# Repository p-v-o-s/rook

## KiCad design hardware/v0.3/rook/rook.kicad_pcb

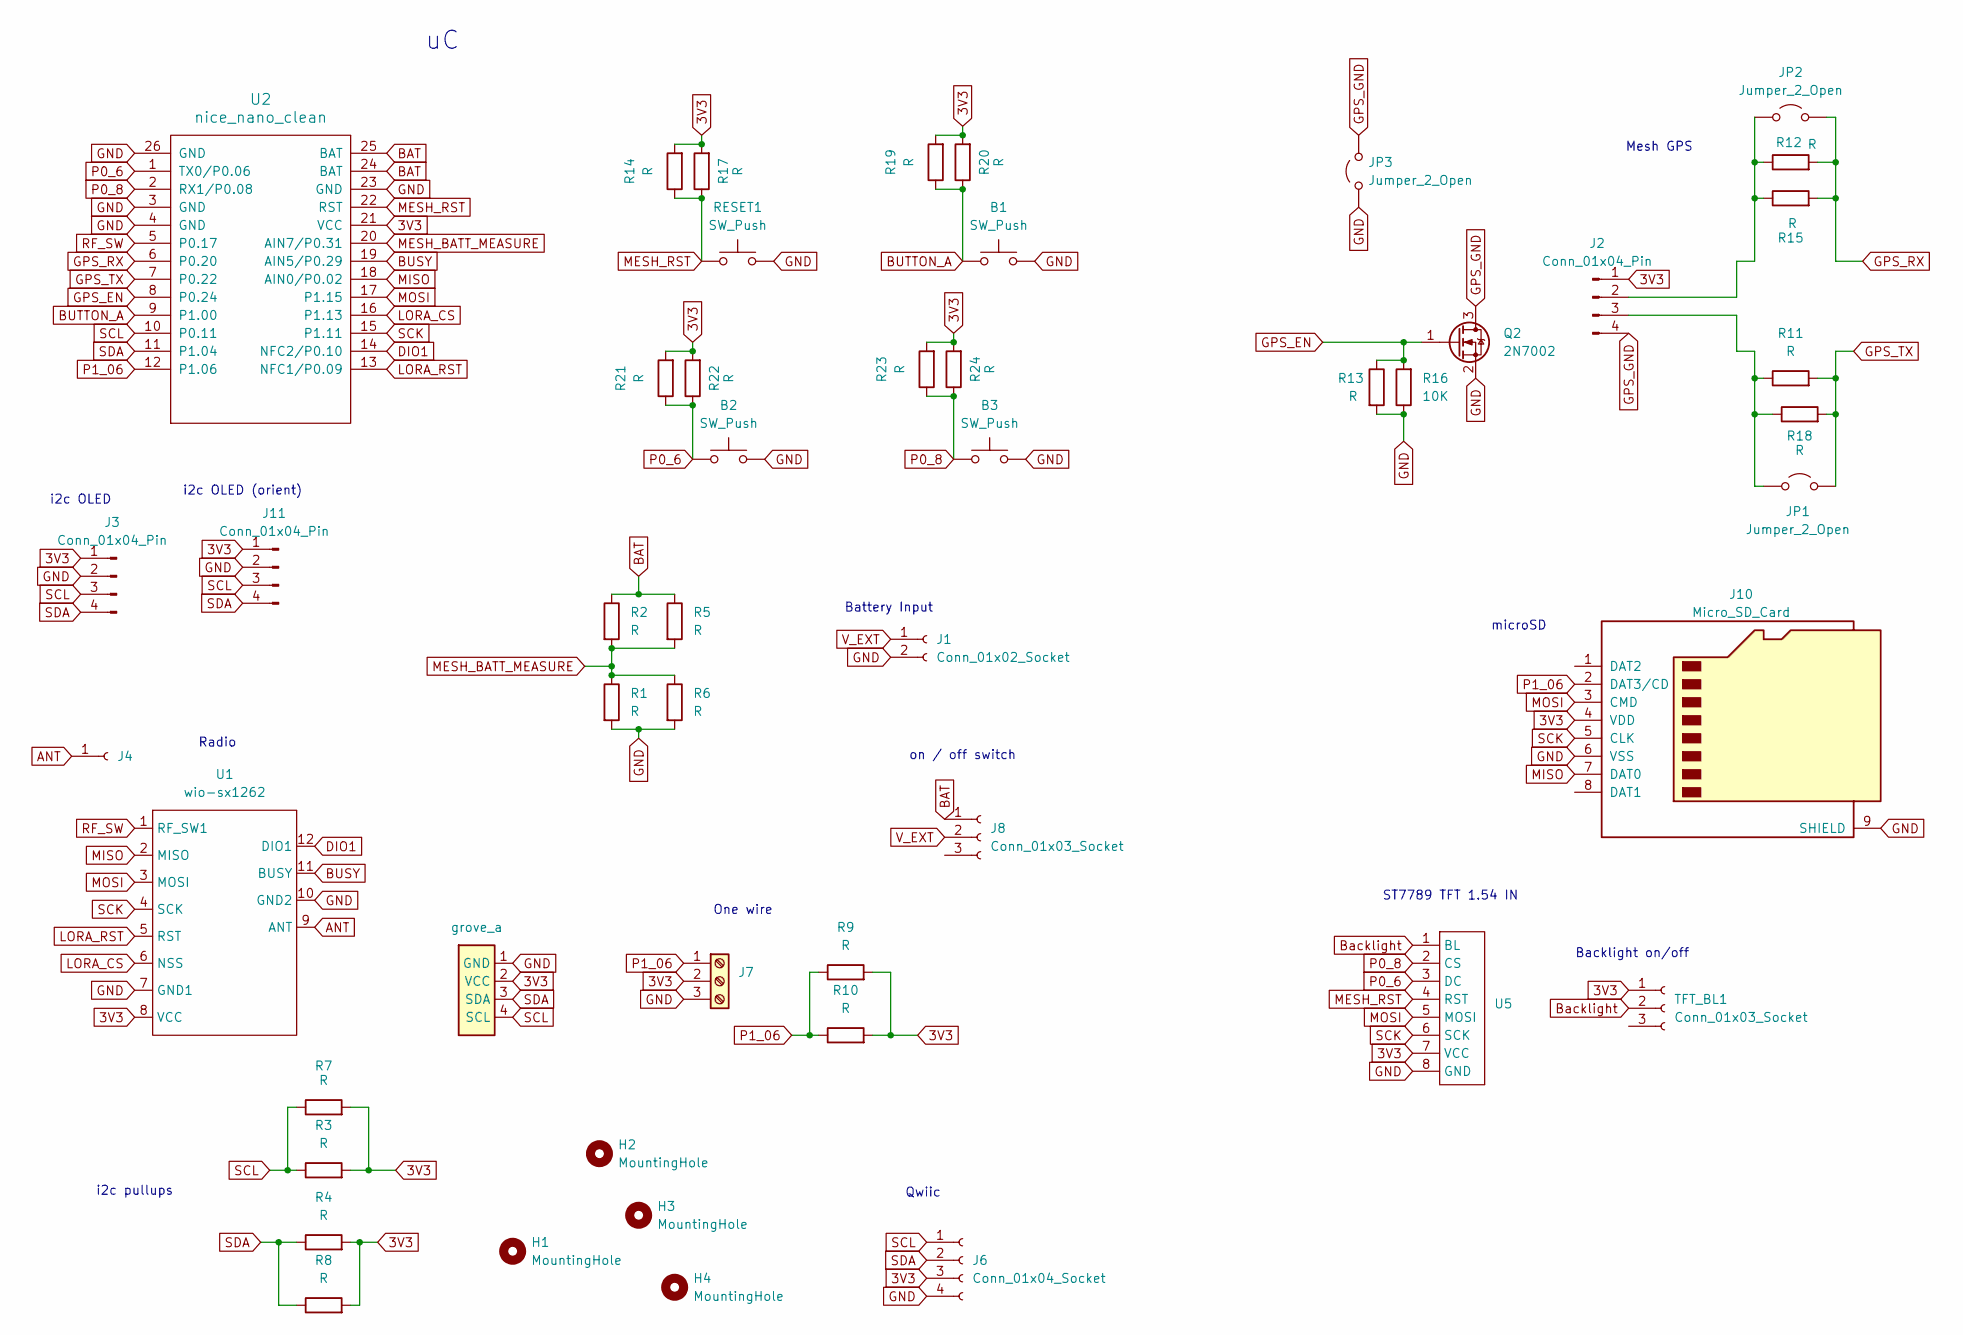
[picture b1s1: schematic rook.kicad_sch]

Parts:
B1, B2, B3: SW_Push; SW_Tactile_SPST_Angled_PTS645Vx31-2LFS
H1, H2, H3, H4: MountingHole; MountingHole_3.2mm_M3
J1: Conn_01x02_Socket; JST_PH_B2B-PH-K_1x02_P2.00mm_Vertical
J2: Conn_01x04_Pin; gps_ublox_blue
J3, J11: Conn_01x04_Pin; ssd1306_a
J4: Conn_01x01_Socket; PinSocket_1x01_P2.54mm_Vertical
J6: Conn_01x04_Socket; JST_SH4_SKINNY
J7: Screw_Terminal_01x03; TerminalBlock_Phoenix_MKDS-1,5-3-5.08_1x03_P5.08mm_Horizont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
J8: Conn_01x03_Socket; SSW_1825232-1
J10: Micro_SD_Card; DM3D-SF_outline
JP1, JP2, JP3: Jumper_2_Open; SolderJumper-2_P1.3mm_Open_Pad1.0x1.5mm
Q2: 2N7002; SOT-23
R1, R2, R3, R4, R10, R11, R12, R13, R14, R19, R21, R23: R; R_Axial_DIN0207_L6.3mm_D2.5mm_P10.16mm_Horizontal
R5, R6, R7, R8, R9, R15, R17, R18, R20, R22, R24: R; R_0805_2012Metric_Pad1.20x1.40mm_HandSolder
R16: 10K; R_0805_2012Metric_Pad1.20x1.40mm_HandSolder
RESET1: SW_Push; SW_Tactile_SPST_Angled_PTS645Vx31-2LFS
TFT_BL1: Conn_01x03_Socket; SSW_1825232-1
U1: wio-sx1262; wio-sx1262-extended
U2: nice_nano_clean; nice_nano_cleanest
U4: grove_a
U5: st7789_154in_240x240

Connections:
3V3: J2.1, J3.1, J6.3, J7.2, J10.4 (VDD), J11.1, R3.2, R4.2, R7.2, R8.2, R9.2, R10.2, R14.2, R17.2, R19.2, R20.2, R21.2, R22.2, R23.2, R24.2, TFT_BL1.1, U1.8 (VCC), U2.21 (VCC), U4.2 (VCC), U5.7 (VCC)
ANT: J4.1, U1.9 (ANT)
BAT: J8.1, R2.1, R5.1, U2.24 (BAT), U2.25 (BAT)
BUSY: U1.11 (BUSY), U2.19 (AIN5/P0.29)
BUTTON_A: B1.1, R19.1, R20.1, U2.9 (P1.00)
Backlight: TFT_BL1.2, U5.1 (BL)
DIO1: U1.12 (DIO1), U2.14 (NFC2/P0.10)
GND: B1.2, B2.2, B3.2, J1.2, J3.2, J6.4, J7.3, J10.6 (VSS), J10.9 (SHIELD), J11.2, JP3.1 (A), Q2.2 (S), R1.2, R6.2, R13.2, R16.1, RESET1.2, U1.7 (GND1), U1.10 (GND2), U2.3 (GND), U2.4 (GND), U2.23 (GND), U2.26 (GND), U4.1 (GND), U5.8 (GND)
GPS_EN: Q2.1 (G), R13.1, R16.2, U2.8 (P0.24)
GPS_GND: J2.4, JP3.2 (B), Q2.3 (D)
GPS_RX: JP2.2 (B), R12.2, R15.2, U2.6 (P0.20)
GPS_TX: JP1.2 (B), R11.2, R18.2, U2.7 (P0.22)
LORA_CS: U1.6 (NSS), U2.16 (P1.13)
LORA_RST: U1.5 (RST), U2.13 (NFC1/P0.09)
MESH_BATT_MEASURE: R1.1, R2.2, R5.2, R6.1, U2.20 (AIN7/P0.31)
MESH_RST: R14.1, R17.1, RESET1.1, U2.22 (RST), U5.4 (RST)
MISO: J10.7 (DAT0), U1.2 (MISO), U2.18 (AIN0/P0.02)
MOSI: J10.3 (CMD), U1.3 (MOSI), U2.17 (P1.15), U5.5 (MOSI)
unnamed: J2.2, JP2.1 (A), R12.1, R15.1
unnamed: J2.3, JP1.1 (A), R11.1, R18.1
P0_6: B2.1, R21.1, R22.1, U2.1 (TX0/P0.06), U5.3 (DC)
P0_8: B3.1, R23.1, R24.1, U2.2 (RX1/P0.08), U5.2 (CS)
P1_06: J7.1, J10.2 (DAT3/CD), R9.1, R10.1, U2.12 (P1.06)
RF_SW: U1.1 (RF_SW1), U2.5 (P0.17)
SCK: J10.5 (CLK), U1.4 (SCK), U2.15 (P1.11), U5.6 (SCK)
SCL: J3.3, J6.1, J11.3, R3.1, R7.1, U2.10 (P0.11), U4.4 (SCL)
SDA: J3.4, J6.2, J11.4, R4.1, R8.1, U2.11 (P1.04), U4.3 (SDA)
V_EXT: J1.1, J8.2

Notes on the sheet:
microSD
Mesh GPS
ST7789 TFT 1.54 IN
Backlight on/off
on / off switch
One wire
i2c pullups
i2c OLED
Radio
i2c OLED (orient)
Battery Input
Qwiic

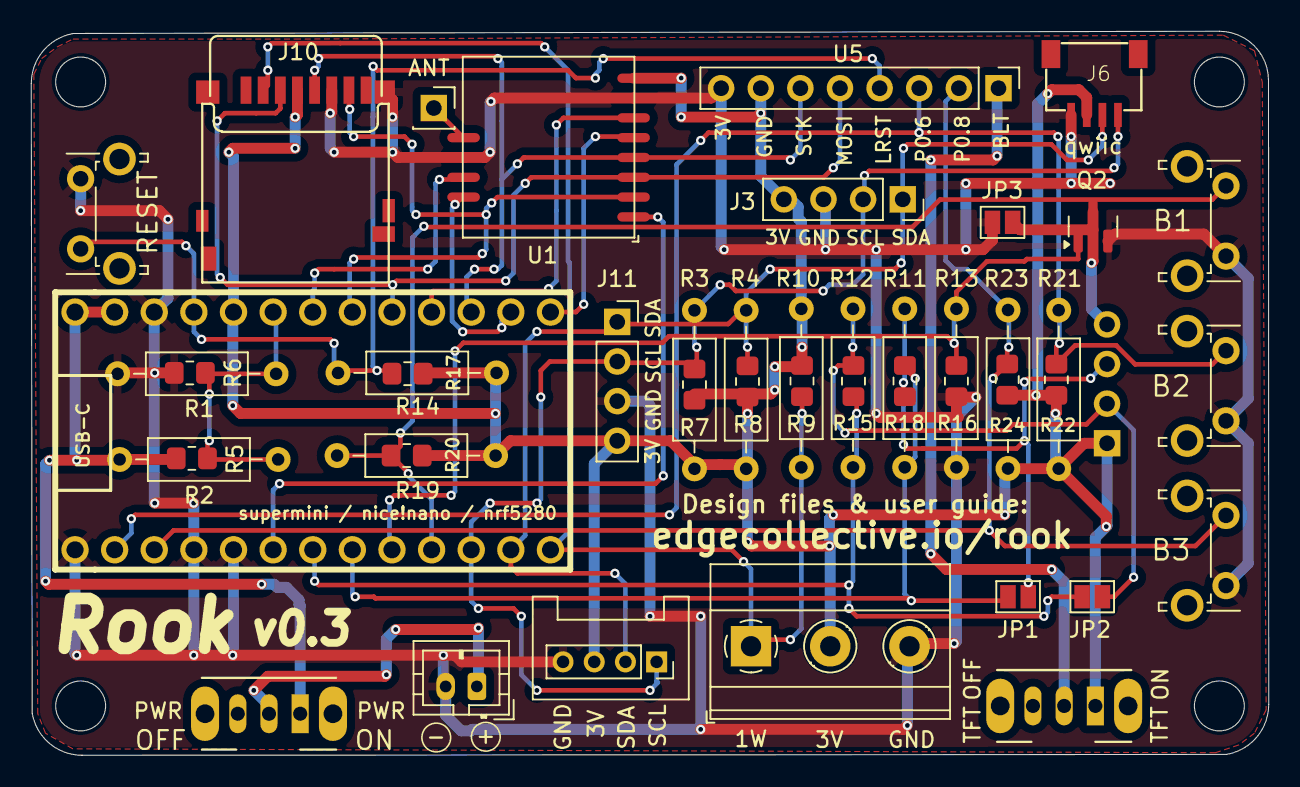
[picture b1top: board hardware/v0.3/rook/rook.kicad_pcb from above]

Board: 2 copper layers, 79.3 x 46.4 mm, 50 parts (1 on the bottom side), 28 nets.

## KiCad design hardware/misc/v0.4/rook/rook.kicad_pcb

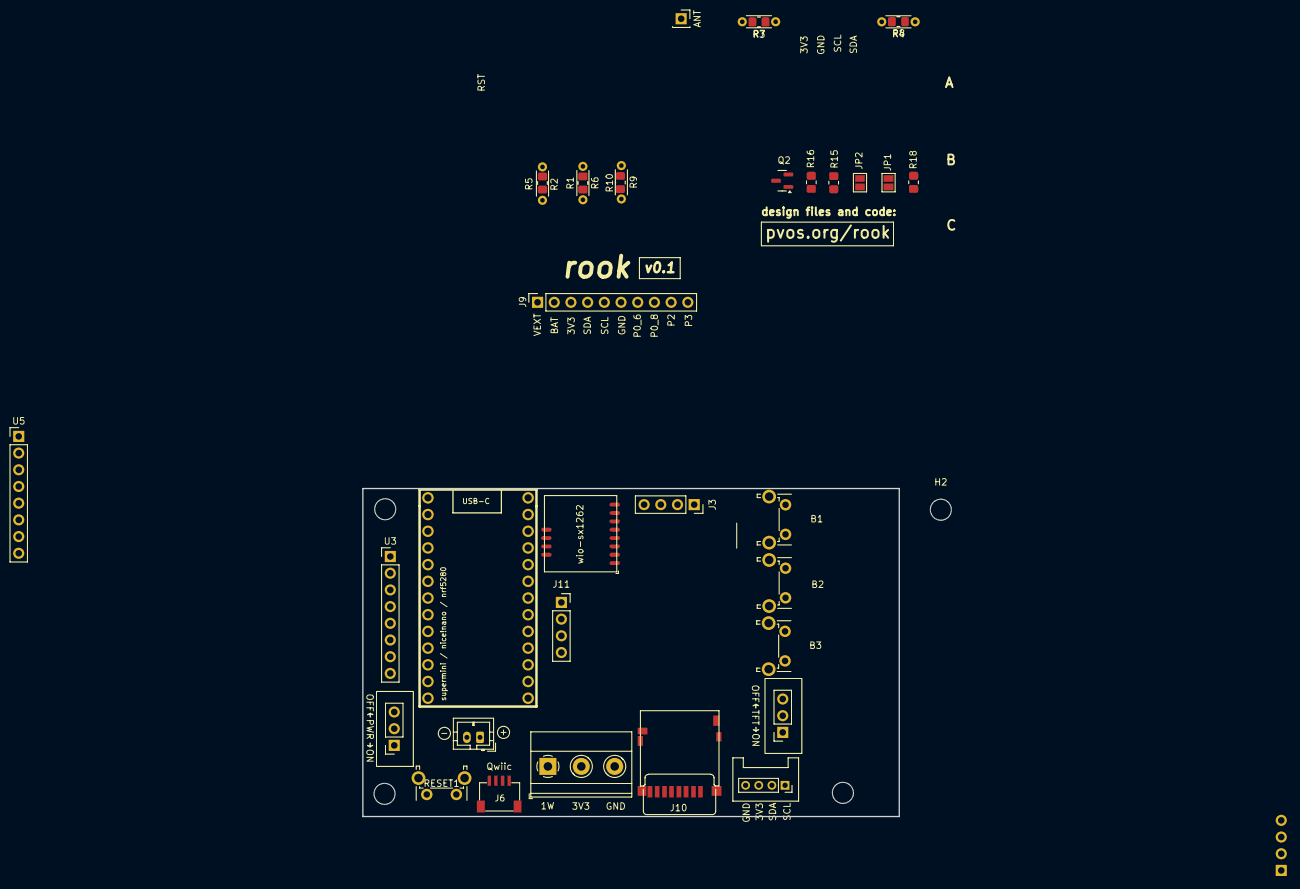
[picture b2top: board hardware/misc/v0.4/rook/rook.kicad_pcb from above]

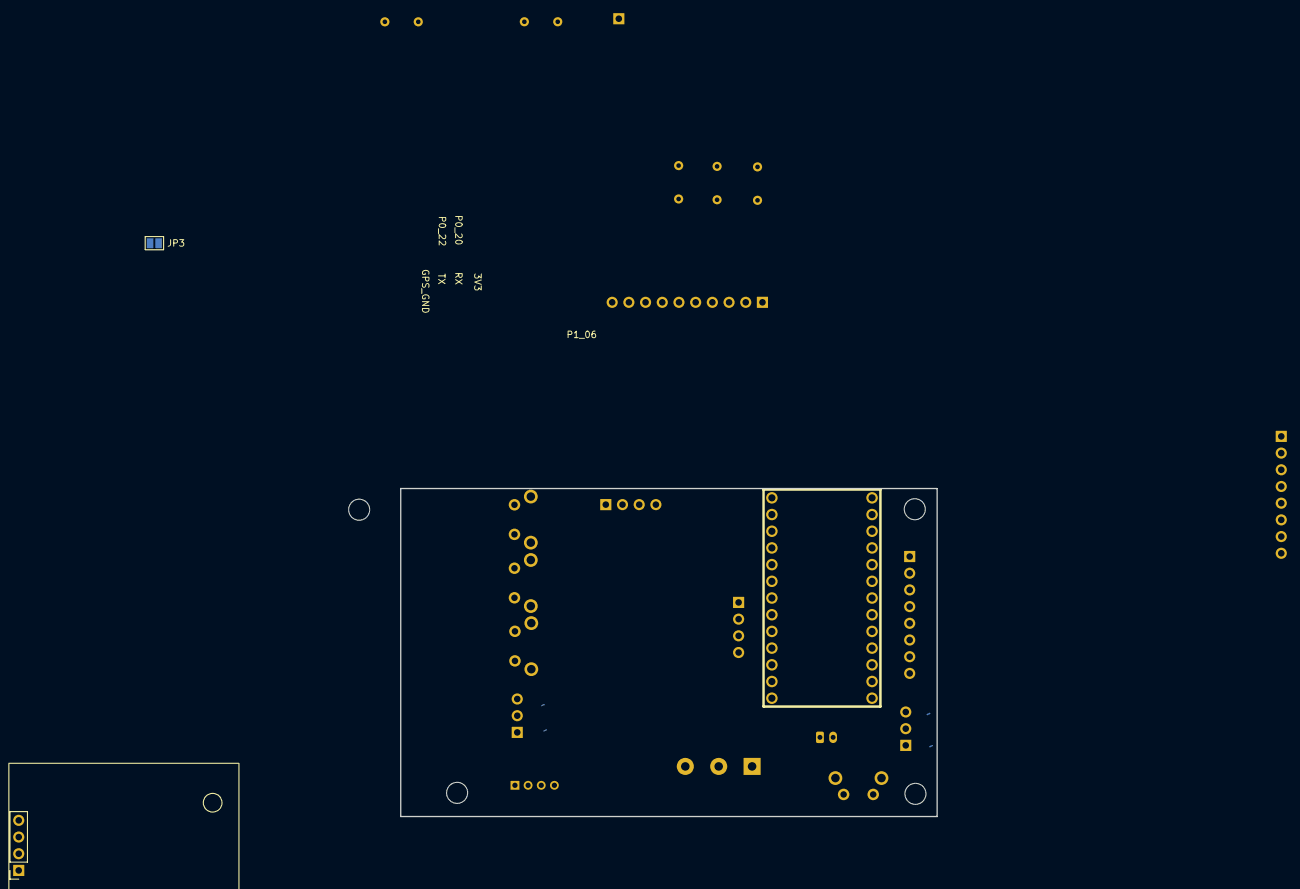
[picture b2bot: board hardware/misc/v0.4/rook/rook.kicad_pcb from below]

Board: 2 copper layers, 81.6 x 49.9 mm, 41 parts (2 on the bottom side), 27 nets, no tracks yet.

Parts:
B1, B2, B3: SW_Push; SW_Tactile_SPST_Angled_PTS645Vx31-2LFS
H1, H2, H3, H4: MountingHole; MountingHole_3.2mm_M3
J1: Conn_01x02_Socket; JST_PH_B2B-PH-K_1x02_P2.00mm_Vertical
J2: Conn_01x04_Pin; gps_ublox_blue
J3, J11: Conn_01x04_Pin; ssd1306_a
J4: Conn_01x01_Socket; PinSocket_1x01_P2.54mm_Vertical
J6: Conn_01x04_Socket; JST_SH4_SKINNY
J7: Screw_Terminal_01x03; TerminalBlock_Phoenix_MKDS-1,5-3-5.08_1x03_P5.08mm_Horizont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
J8: Conn_01x03_Socket; usual_switch
J9: Conn_01x10_Socket; PinSocket_1x10_P2.54mm_Vertical
J10: Micro_SD_Card; DM3D-SF_outline
JP1, JP2, JP3: Jumper_2_Open; SolderJumper-2_P1.3mm_Open_Pad1.0x1.5mm
Q2: 2N7002; SOT-23
R1, R2, R3, R4, R10: R; R_Axial_DIN0204_L3.6mm_D1.6mm_P5.08mm_Horizontal
R5, R6, R7, R8, R9, R15, R18: R; R_0805_2012Metric_Pad1.20x1.40mm_HandSolder
R16: 10K; R_0805_2012Metric_Pad1.20x1.40mm_HandSolder
RESET1: SW_Push; SW_Tactile_SPST_Angled_PTS645Vx31-2LFS
TFT_BL1: Conn_01x03_Socket; usual_switch
U1: wio-sx1262
U2: nice_nano_clean; nice_nano_cleanest
U3: st7789_tft_2in_320x240
U4: grove_a
U5: st7789_154in_240x240

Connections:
3V3: J2.1, J3.1, J6.3, J7.2, J9.3, J10.4 (VDD), J11.1, R3.2, R4.2, R7.2, R8.2, R9.2, R10.2, TFT_BL1.1, U1.8 (VCC), U2.21 (VCC), U3.1 (VCC), U4.2 (VCC), U5.1 (VCC)
ANT: J4.1, U1.9 (ANT)
BAT: J8.1, J9.2, R2.1, R5.1, U2.24 (BAT), U2.25 (BAT)
BUSY: U1.11 (BUSY), U2.19 (AIN5/P0.29)
BUTTON_A: B1.1, U2.9 (P1.00)
DIO1: U1.12 (DIO1), U2.14 (NFC2/P0.10)
GND: B1.2, B2.2, B3.2, J1.2, J3.2, J6.4, J7.3, J9.6, J10.6 (VSS), J10.9 (SHIELD), J11.2, JP3.1 (A), Q2.2 (S), R1.2, R6.2, R16.1, RESET1.2, U1.7 (GND1), U1.10 (GND2), U2.3 (GND), U2.4 (GND), U2.23 (GND), U2.26 (GND), U4.1 (GND)
GPS_EN: Q2.1 (G), R16.2, U2.8 (P0.24)
GPS_GND: J2.4, JP3.2 (B), Q2.3 (D)
GPS_RX: JP2.2 (B), R15.2, U2.6 (P0.20)
GPS_TX: JP1.2 (B), R18.2, U2.7 (P0.22)
LORA_CS: U1.6 (NSS), U2.16 (P1.13)
LORA_RST: U1.5 (RST), U2.13 (NFC1/P0.09)
MESH_BATT_MEASURE: R1.1, R2.2, R5.2, R6.1, U2.20 (AIN7/P0.31)
MESH_RST: RESET1.1, U2.22 (RST)
MISO: J10.7 (DAT0), U1.2 (MISO), U2.18 (AIN0/P0.02)
MOSI: J10.3 (CMD), U1.3 (MOSI), U2.17 (P1.15)
unnamed: J2.2, JP2.1 (A), R15.1
unnamed: J2.3, JP1.1 (A), R18.1
P0_6: B2.1, J9.7, U2.1 (TX0/P0.06)
P0_8: B3.1, J9.8, U2.2 (RX1/P0.08)
P1_06: J7.1, J10.2 (DAT3/CD), R9.1, R10.1, U2.12 (P1.06)
RF_SW: U1.1 (RF_SW1), U2.5 (P0.17)
SCK: J10.5 (CLK), U1.4 (SCK), U2.15 (P1.11)
SCL: J3.3, J6.1, J9.5, J11.3, R3.1, R7.1, U2.10 (P0.11), U4.4 (SCL)
SDA: J3.4, J6.2, J9.4, J11.4, R4.1, R8.1, U2.11 (P1.04), U4.3 (SDA)
V_EXT: J1.1, J8.2, J9.1

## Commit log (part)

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2025-12-02 udpate
2026-02-28 new layout
2026-02-28 tweaks
2026-02-28 finished routing
